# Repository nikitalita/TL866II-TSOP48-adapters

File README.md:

# TL866II-TSOP48-adapters

WARNING: COMPLETELY UNTESTED

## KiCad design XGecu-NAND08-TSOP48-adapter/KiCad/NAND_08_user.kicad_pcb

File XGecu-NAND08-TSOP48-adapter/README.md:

This is an port of the official XGecu TSOP48 design files that were posted on their website from Altium to KiCad. Used for reference.

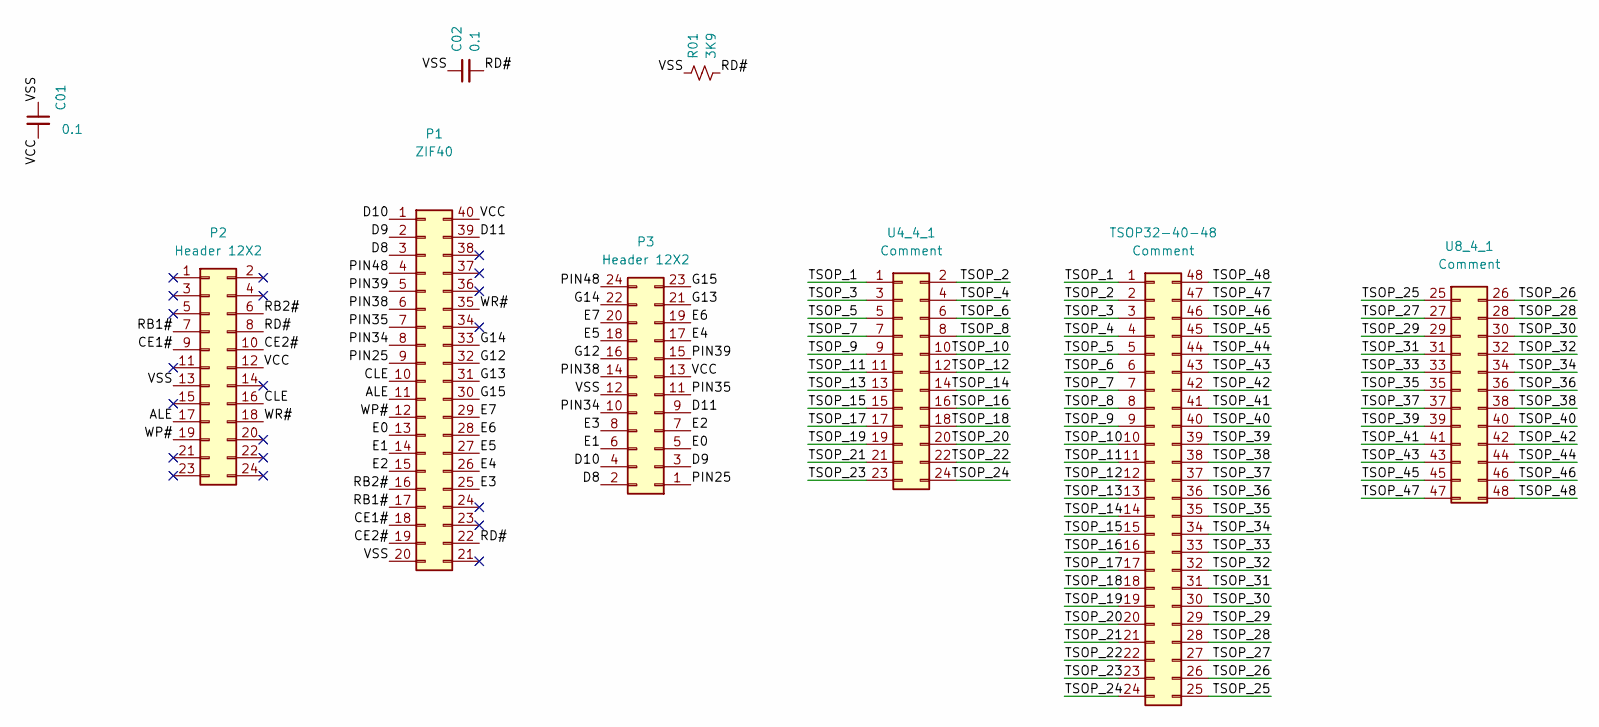
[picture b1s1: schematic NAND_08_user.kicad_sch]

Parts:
C01: 0.1; C01
C02: 0.1; C02
P1: ZIF40; P1
P2: Header 12X2; P2
P3: Header 12X2; P3
R01: 3K9; R01
TSOP32-40-48: Comment; TSOP32-40-48
U4_4_1: Comment; U4_4_1
U8_4_1: Comment; U8_4_1

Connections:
/ALE: P1.11, P2.17
/CE1#: P1.18, P2.9
/CE2#: P1.19, P2.10
/CLE: P1.10, P2.16
/D8: P1.3, P3.2
/D9: P1.2, P3.3
/D10: P1.1, P3.4
/D11: P1.39, P3.9
/E0: P1.13, P3.5
/E1: P1.14, P3.6
/E2: P1.15, P3.7
/E3: P1.25, P3.8
/E4: P1.26, P3.17
/E5: P1.27, P3.18
/E6: P1.28, P3.19
/E7: P1.29, P3.20
/G12: P1.32, P3.16
/G13: P1.31, P3.21
/G14: P1.33, P3.22
/G15: P1.30, P3.23
/PIN25: P1.9, P3.1
/PIN34: P1.8, P3.10
/PIN35: P1.7, P3.11
/PIN38: P1.6, P3.14
/PIN39: P1.5, P3.15
/PIN48: P1.4, P3.24
/RB1#: P1.17, P2.7
/RB2#: P1.16, P2.6
/RD#: C02.2, P1.22, P2.8, R01.2
/TSOP_1: TSOP32-40-48.1, U4_4_1.1
/TSOP_2: TSOP32-40-48.2, U4_4_1.2
/TSOP_3: TSOP32-40-48.3, U4_4_1.3
/TSOP_4: TSOP32-40-48.4, U4_4_1.4
/TSOP_5: TSOP32-40-48.5, U4_4_1.5
/TSOP_6: TSOP32-40-48.6, U4_4_1.6
/TSOP_7: TSOP32-40-48.7, U4_4_1.7
/TSOP_8: TSOP32-40-48.8, U4_4_1.8
/TSOP_9: TSOP32-40-48.9, U4_4_1.9
/TSOP_10: TSOP32-40-48.10, U4_4_1.10
/TSOP_11: TSOP32-40-48.11, U4_4_1.11
/TSOP_12: TSOP32-40-48.12, U4_4_1.12
/TSOP_13: TSOP32-40-48.13, U4_4_1.13
/TSOP_14: TSOP32-40-48.14, U4_4_1.14
/TSOP_15: TSOP32-40-48.15, U4_4_1.15
/TSOP_16: TSOP32-40-48.16, U4_4_1.16
/TSOP_17: TSOP32-40-48.17, U4_4_1.17
/TSOP_18: TSOP32-40-48.18, U4_4_1.18
/TSOP_19: TSOP32-40-48.19, U4_4_1.19
/TSOP_20: TSOP32-40-48.20, U4_4_1.20
/TSOP_21: TSOP32-40-48.21, U4_4_1.21
/TSOP_22: TSOP32-40-48.22, U4_4_1.22
/TSOP_23: TSOP32-40-48.23, U4_4_1.23
/TSOP_24: TSOP32-40-48.24, U4_4_1.24
/TSOP_25: TSOP32-40-48.25, U8_4_1.25 (Pin_3)
/TSOP_26: TSOP32-40-48.26, U8_4_1.26 (Pin_4)
/TSOP_27: TSOP32-40-48.27, U8_4_1.27 (Pin_5)
/TSOP_28: TSOP32-40-48.28, U8_4_1.28 (Pin_6)
/TSOP_29: TSOP32-40-48.29, U8_4_1.29 (Pin_7)
/TSOP_30: TSOP32-40-48.30, U8_4_1.30 (Pin_8)
/TSOP_31: TSOP32-40-48.31, U8_4_1.31 (Pin_9)
/TSOP_32: TSOP32-40-48.32, U8_4_1.32 (Pin_10)
/TSOP_33: TSOP32-40-48.33, U8_4_1.33 (Pin_11)
/TSOP_34: TSOP32-40-48.34, U8_4_1.34 (Pin_12)
/TSOP_35: TSOP32-40-48.35, U8_4_1.35 (Pin_13)
/TSOP_36: TSOP32-40-48.36, U8_4_1.36 (Pin_14)
/TSOP_37: TSOP32-40-48.37, U8_4_1.37 (Pin_15)
/TSOP_38: TSOP32-40-48.38, U8_4_1.38 (Pin_16)
/TSOP_39: TSOP32-40-48.39, U8_4_1.39 (Pin_17)
/TSOP_40: TSOP32-40-48.40, U8_4_1.40 (Pin_18)
/TSOP_41: TSOP32-40-48.41, U8_4_1.41 (Pin_19)
/TSOP_42: TSOP32-40-48.42, U8_4_1.42 (Pin_20)
/TSOP_43: TSOP32-40-48.43, U8_4_1.43 (Pin_21)
/TSOP_44: TSOP32-40-48.44, U8_4_1.44 (Pin_22)
/TSOP_45: TSOP32-40-48.45, U8_4_1.45 (Pin_1)
/TSOP_46: TSOP32-40-48.46, U8_4_1.46 (Pin_2)
/TSOP_47: TSOP32-40-48.47, U8_4_1.47 (Pin_23)
/TSOP_48: TSOP32-40-48.48, U8_4_1.48 (Pin_24)
/VCC: C01.2, P1.40, P2.12, P3.13
/VSS: C01.1, C02.1, P1.20, P2.13, P3.12, R01.1
/WP#: P1.12, P2.19
/WR#: P1.35, P2.18

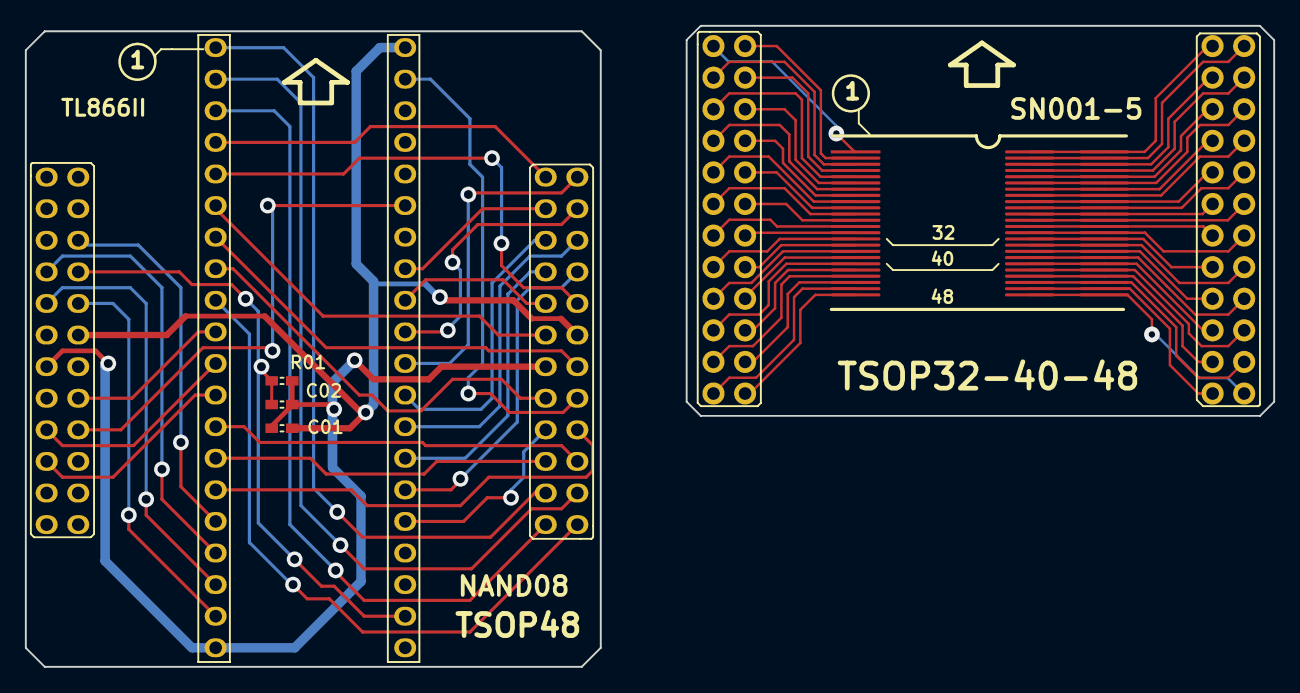
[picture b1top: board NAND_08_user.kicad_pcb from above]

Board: 2 copper layers, 100.4 x 51.5 mm, 9 parts (0 on the bottom side), 81 nets.

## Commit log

2022-04-04 Add files
2022-07-29 next rev of tsop48-to-dip42
2022-07-29 Added port of the official XGecu TSOP48 adapter
